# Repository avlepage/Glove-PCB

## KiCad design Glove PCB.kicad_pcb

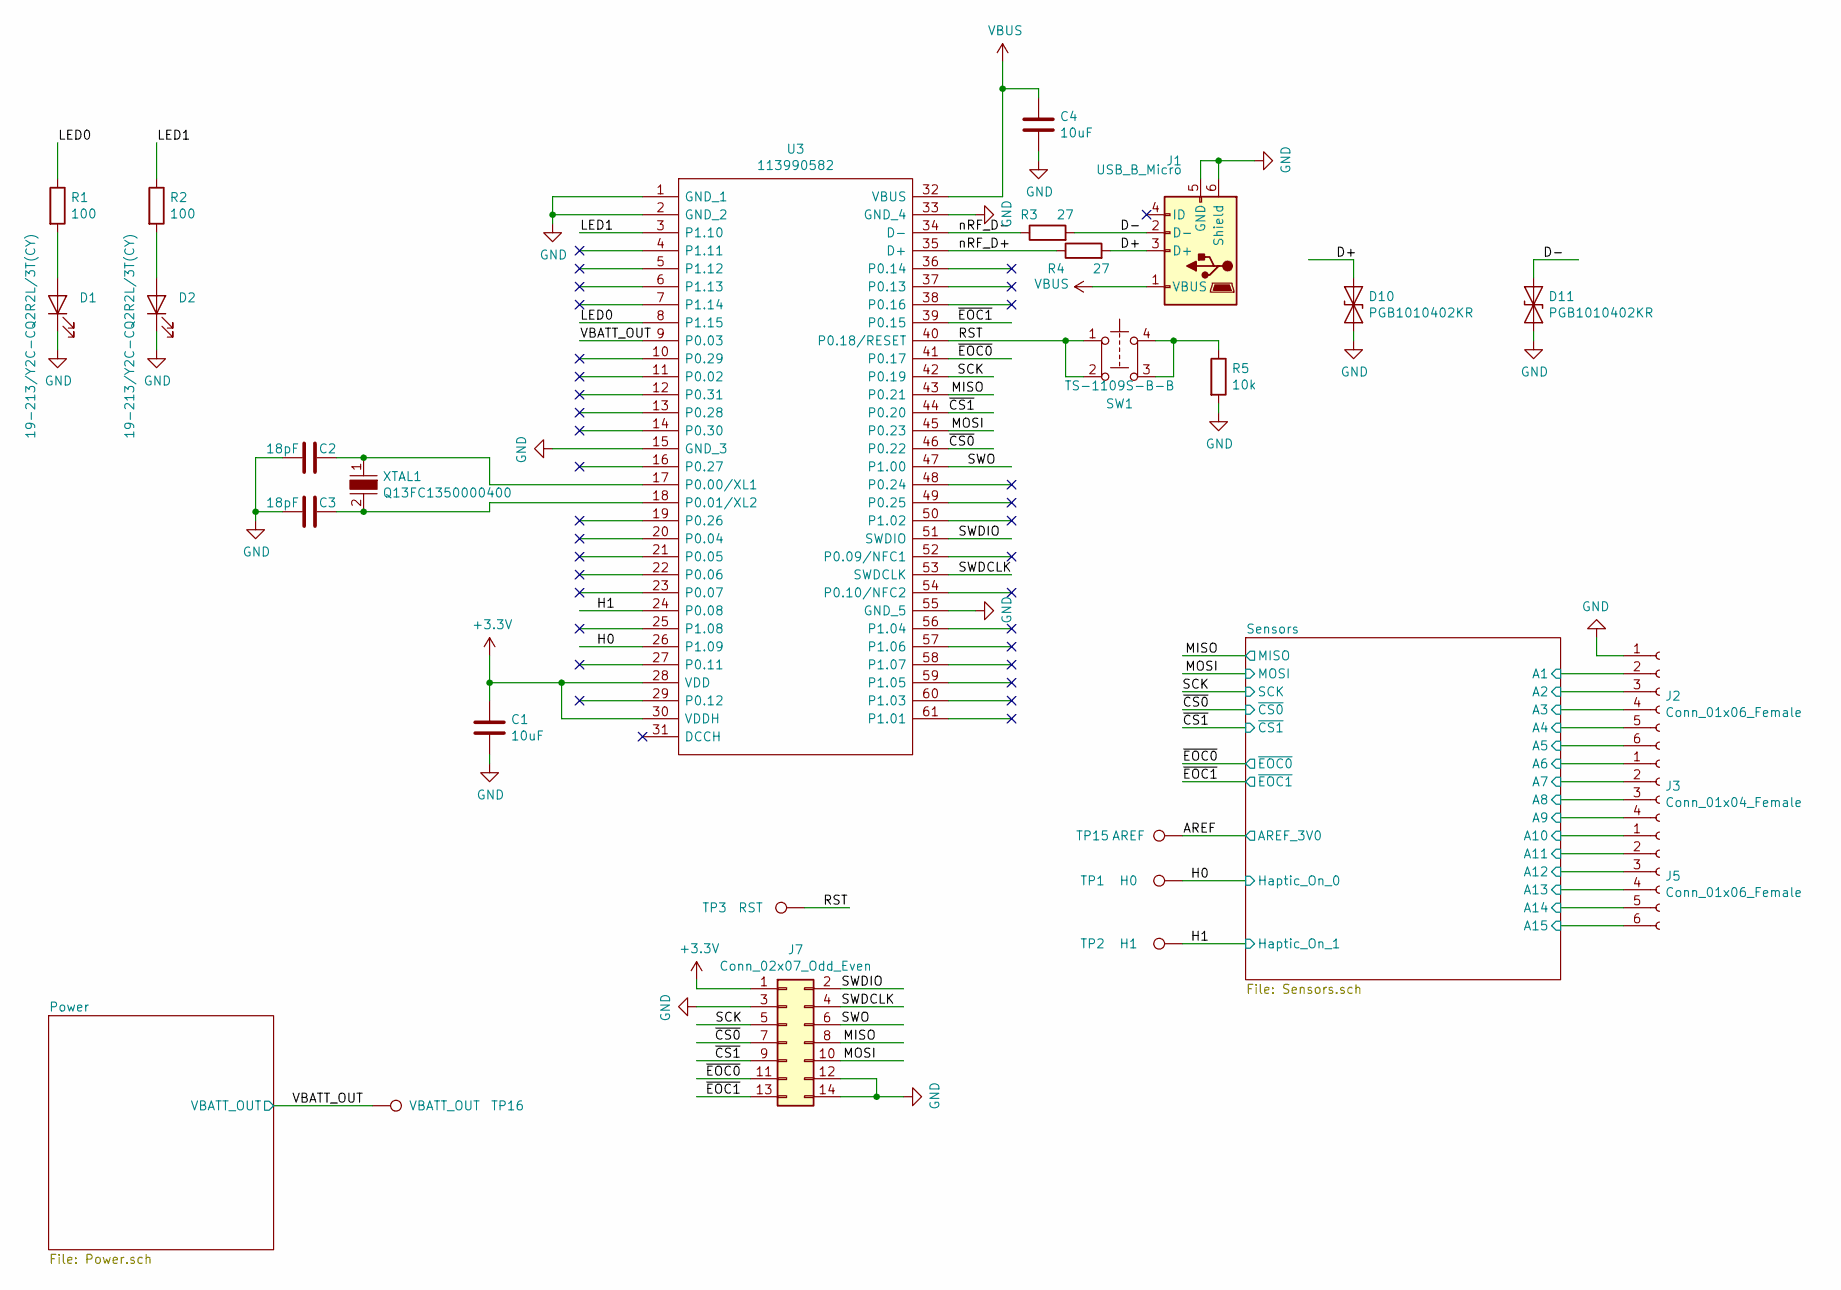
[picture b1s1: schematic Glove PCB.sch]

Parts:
C1, C4: 10uF; C_0603_HandSoldering; MPN CL10A106KP8NNNC; LCSC C19702
C2, C3: 18pF; C_0402; MPN 0402CG180J500NT; LCSC C1549
D1, D2: 19-213/Y2C-CQ2R2L/3T(CY); LED_0603_HandSoldering; MPN 19-213/Y2C-CQ2R2L/3T(CY); LCSC C72038
D10, D11: PGB1010402KR; D_0402_1005Metric; MPN PGB1010402KR; LCSC C10676
J1: USB_B_Micro; USB_Micro-B_10118194-0001LF
J2, J5: Conn_01x06_Female; 22-05-7065
J3: Conn_01x04_Female; 22-05-7045
J7: Conn_02x07_Odd_Even; PinHeader_2x07_P2.54mm_Vertical
R1, R2: 100; R_0603_HandSoldering; MPN 0603WAF1000T5E; LCSC C22775
R3, R4: 27; R_0603_1608Metric_Pad0.84x1.00mm_HandSolder; MPN 0603WAF270JT5E; LCSC C25190
R5: 10k; R_0402_1005Metric; MPN 0402WGF1002TCE; LCSC C25744
SW1: TS-1109S-B-B; Button; MPN TS-1109S-B-B; LCSC C480315
TP1: H0; TestPoint_Pad_D1.5mm
TP2: H1; TestPoint_Pad_D1.5mm
TP3: RST; TestPoint_Pad_D1.5mm
TP15: AREF; TestPoint_Pad_D1.5mm
TP16: VBATT_OUT; TestPoint_Pad_D1.5mm
U3: 113990582; Mouser Part Number 713-113990582
XTAL1: Q13FC1350000400; Crystal_SMD_G8-2pin_3.2x1.5mm; MPN Q13FC1350000400; Digi-Key_PN XC1617CT-ND

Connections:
+3V3: C1.1, J7.1, U3.28 (VDD), U3.30 (VDDH); also elsewhere on the board
/AREF: TP15.1; also elsewhere on the board
/D+: D10.1 (A1), J1.3 (D+), R4.2
/D-: D11.1 (A1), J1.2 (D-), R3.2
/H0: TP1.1, U3.26 (P1.09); also elsewhere on the board
/H1: TP2.1, U3.24 (P0.08); also elsewhere on the board
/LED0: R1.1, U3.8 (P1.15)
/LED1: R2.1, U3.3 (P1.10)
/MISO: J7.8, U3.43 (P0.21); also elsewhere on the board
/MOSI: J7.10, U3.45 (P0.23); also elsewhere on the board
/RST: SW1.1, SW1.2, TP3.1, U3.40 (P0.18/RESET); also elsewhere on the board
/SCK: J7.5, U3.42 (P0.19); also elsewhere on the board
/SWDCLK: J7.4, U3.53 (SWDCLK)
/SWDIO: J7.2, U3.51 (SWDIO)
/SWO: J7.6, U3.47 (P1.00)
/Sensors/A1: J2.2; also elsewhere on the board
/Sensors/A2: J2.3; also elsewhere on the board
/Sensors/A3: J2.4; also elsewhere on the board
/Sensors/A4: J2.5; also elsewhere on the board
/Sensors/A5: J2.6; also elsewhere on the board
/Sensors/A6: J3.1; also elsewhere on the board
/Sensors/A7: J3.2; also elsewhere on the board
/Sensors/A8: J3.3; also elsewhere on the board
/Sensors/A9: J3.4; also elsewhere on the board
/Sensors/A10: J5.1; also elsewhere on the board
/Sensors/A11: J5.2; also elsewhere on the board
/Sensors/A12: J5.3; also elsewhere on the board
/Sensors/A13: J5.4; also elsewhere on the board
/Sensors/A14: J5.5; also elsewhere on the board
/Sensors/A15: J5.6; also elsewhere on the board
/VBATT_OUT: TP16.1, U3.9 (P0.03); also elsewhere on the board
/nRF_D+: R4.1, U3.35 (D+)
/nRF_D-: R3.1, U3.34 (D-)
/~CS0: J7.7, U3.46 (P0.22); also elsewhere on the board
/~CS1: J7.9, U3.44 (P0.20); also elsewhere on the board
/~EOC0: J7.11, U3.41 (P0.17); also elsewhere on the board
/~EOC1: J7.13, U3.39 (P0.15); also elsewhere on the board
GND: C1.2, C2.2, C3.2, C4.2, D1.1 (K), D2.1 (K), D10.2 (A2), D11.2 (A2), J1.5 (GND), J1.6 (Shield), J2.1, J7.3, J7.12, J7.14, R5.2, U3.1 (GND_1), U3.2 (GND_2), U3.15 (GND_3), U3.33 (GND_4), U3.55 (GND_5); also elsewhere on the board
unnamed: C2.1, U3.17 (P0.00/XL1), XTAL1.1
unnamed: C3.1, U3.18 (P0.01/XL2), XTAL1.2
unnamed: D1.2 (A), R1.2
unnamed: D2.2 (A), R2.2
unnamed: R5.1, SW1.3, SW1.4
VBUS: C4.1, J1.1 (VBUS), U3.32 (VBUS); also elsewhere on the board

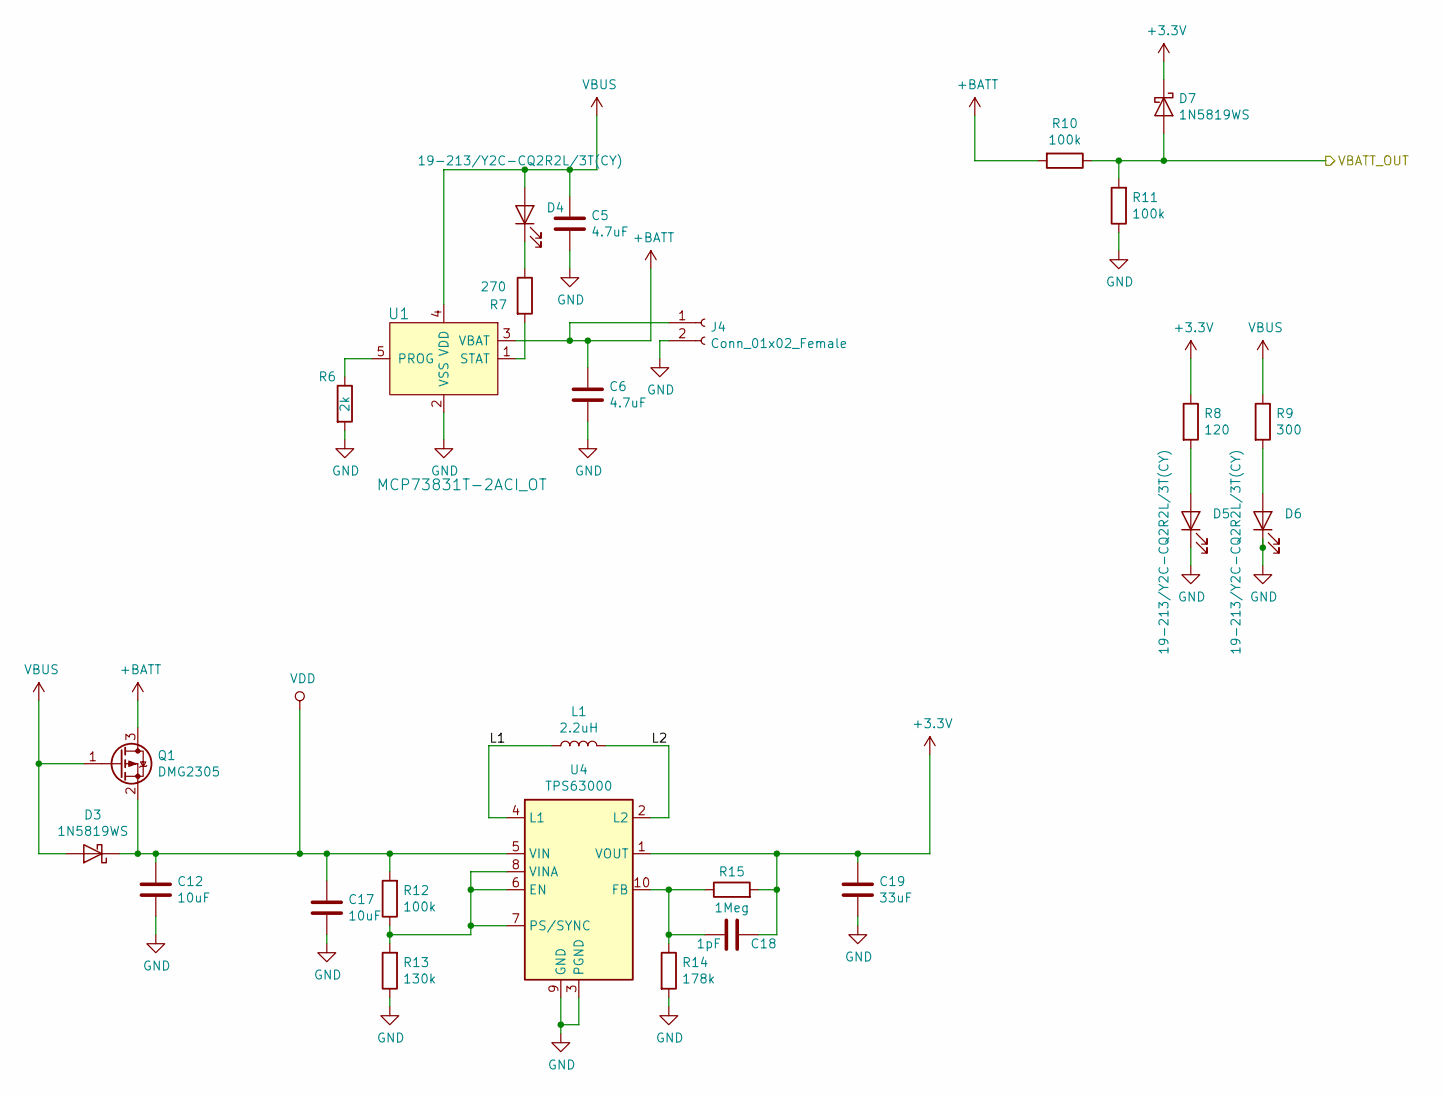
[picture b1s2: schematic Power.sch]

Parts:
C5, C6: 4.7uF; C_0603_HandSoldering; MPN CL10A475KO8NNNC; LCSC C19666
C12, C17: 10uF; C_0603_HandSoldering; MPN CL10A106KP8NNNC; LCSC C19702
C18: 1pF; C_0603_HandSoldering; MPN CL10C010CB8NNNC; LCSC C23969
C19: 33uF; C_0805_HandSoldering; MPN C2012X5R1A336MTJ00E; LCSC C342635
D3, D7: 1N5819WS; D_SOD-323; MPN 1N5819WS; LCSC C191023
D4, D5, D6: 19-213/Y2C-CQ2R2L/3T(CY); LED_0603_HandSoldering; MPN 19-213/Y2C-CQ2R2L/3T(CY); LCSC C72038
J4: Conn_01x02_Female; JST_PH_B2B-PH-SM4-TB_1x02_P2.00mm_Vertical
L1: 2.2uH; L_0805_HandSoldering; MPN MPH201210S2R2MT; LCSC C55755
Q1: DMG2305; SOT-23; MPN DMG2305UX-13; LCSC C144153
R6: 2k; R_0402_1005Metric; MPN 0402WGF2001TCE; LCSC C4109
R7: 270; R_0603_HandSoldering; MPN 0603WAF2700T5E; LCSC C22966
R8: 120; R_0603_HandSoldering; MPN 0603WAF1200T5E; LCSC C22787
R9: 300; R_0603_HandSoldering; MPN 0603WAF3000T5E; LCSC C23025
R10, R11, R12: 100k; R_0603_HandSoldering; MPN 0603WAF1003T5E; LCSC C25803
R13: 130k; R_0603_HandSoldering; MPN 0603WAF1303T5E; LCSC C22795
R14: 178k; R_0603_HandSoldering; MPN 0603WAF1783T5E; LCSC C22823
R15: 1Meg; R_0603_HandSoldering; MPN 0603WAF1004T5E; LCSC C22935
U1: MCP73831T-2ACI_OT; SOT-753; MPN MCP73831T-2ACI/OT; Digi-Key_PN MCP73831T-2ACI/OTCT-ND
U4: TPS63000; VSON-10-1EP_3x3mm_P0.5mm_EP1.65x2.4mm_ThermalVias; MPN TPS63000DRCR; LCSC C24966

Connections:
+3V3: C18.1, C19.1, D7.1 (K), R8.1, R15.2, U4.1 (VOUT); also elsewhere on the board
+BATT: C6.1, J4.1, Q1.3 (D), R10.2, U1.3 (VBAT)
/Power/L1: L1.1, U4.4 (L1)
/Power/L2: L1.2, U4.2 (L2)
/VBATT_OUT: D7.2 (A), R10.1, R11.2; also elsewhere on the board
GND: C5.2, C6.2, C12.2, C17.2, C19.2, D5.1 (K), D6.1 (K), J4.2, R6.2, R11.1, R13.1, R14.2, U1.2 (VSS), U4.3 (PGND), U4.9 (GND), U4.11 (PGND); also elsewhere on the board
unnamed: C18.2, R14.1, R15.1, U4.10 (FB)
unnamed: D4.1 (K), R7.1
unnamed: D5.2 (A), R8.2
unnamed: D6.2 (A), R9.2
unnamed: R6.1, U1.5 (PROG)
unnamed: R7.2, U1.1 (STAT)
unnamed: R12.1, R13.2, U4.6 (EN), U4.7 (PS/SYNC), U4.8 (VINA)
VBUS: C5.1, D3.2 (A), D4.2 (A), Q1.1 (G), R9.1, U1.4 (VDD); also elsewhere on the board
VDD: C12.1, C17.1, D3.1 (K), Q1.2 (S), R12.2, U4.5 (VIN); also elsewhere on the board

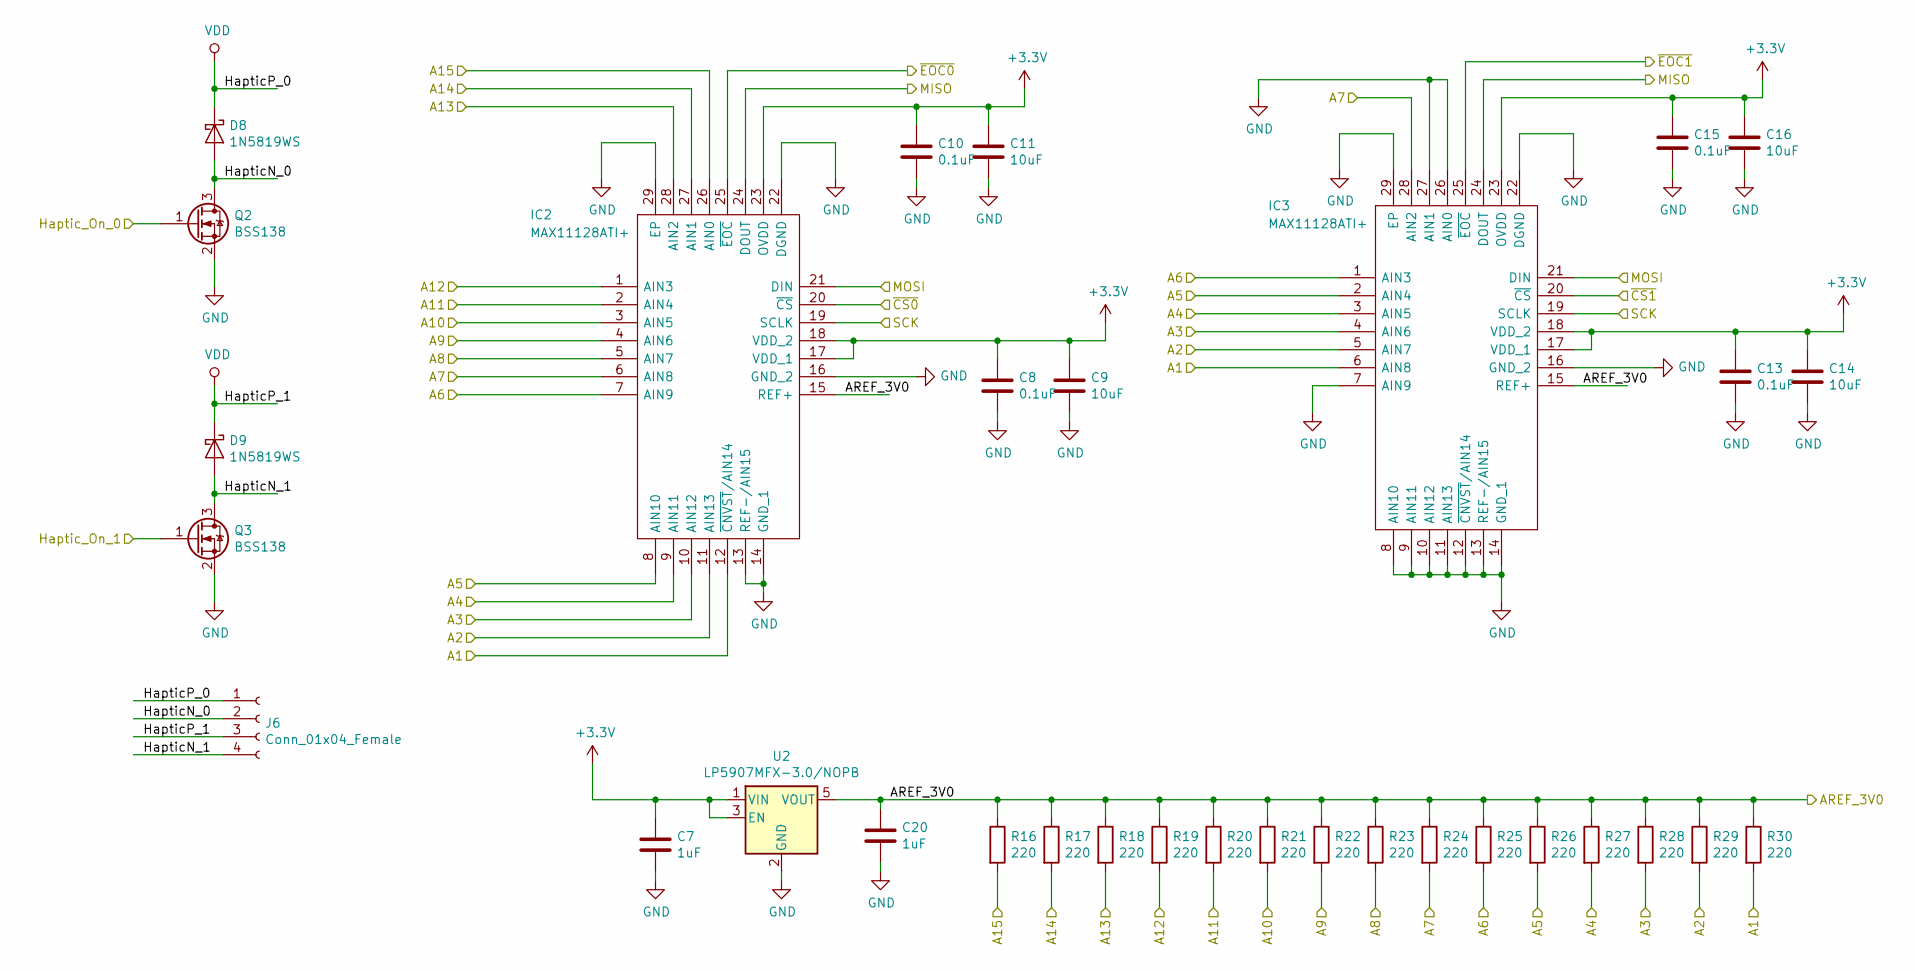
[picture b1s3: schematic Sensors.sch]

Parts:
C7, C20: 1uF; C_0603_HandSoldering; MPN CL10A105KB8NNNC; LCSC C15849
C8, C10, C13, C15: 0.1uF; C_0603_HandSoldering; MPN CC0603KRX7R9BB104; LCSC C14663
C9, C11, C14, C16: 10uF; C_0603_HandSoldering; MPN CL10A106KP8NNNC; LCSC C19702
D8, D9: 1N5819WS; D_SOD-323; MPN 1N5819WS; LCSC C191023
IC2, IC3: MAX11128ATI+; QFN50P500X500X80-29N; Mouser Part Number 700-MAX11128ATI+
J6: Conn_01x04_Female; 22-05-7045
Q2, Q3: BSS138; SOT-23; MPN BSS138; LCSC C52895
R16, R17, R18, R19, R20, R21, R22, R23, R24, R25, R26, R27, R28, R29, R30: 220; R_0603_HandSoldering; MPN 0603WAF2200T5E; LCSC C22962
U2: LP5907MFX-3.0/NOPB; SOT-23-5; MPN LP5907MFX-3.0/NOPB; LCSC C475492

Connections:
+3V3: C7.1, C8.1, C9.1, C10.1, C11.1, C13.1, C14.1, C15.1, C16.1, IC2.17 (VDD_1), IC2.18 (VDD_2), IC2.23 (OVDD), IC3.17 (VDD_1), IC3.18 (VDD_2), IC3.23 (OVDD), U2.1 (VIN), U2.3 (EN); also elsewhere on the board
/AREF: C20.1, IC2.15 (REF+), IC3.15 (REF+), R16.1, R17.1, R18.1, R19.1, R20.1, R21.1, R22.1, R23.1, R24.1, R25.1, R26.1, R27.1, R28.1, R29.1, R30.1, U2.5 (VOUT); also elsewhere on the board
/H0: Q2.1 (G); also elsewhere on the board
/H1: Q3.1 (G); also elsewhere on the board
/MISO: IC2.24 (DOUT), IC3.24 (DOUT); also elsewhere on the board
/MOSI: IC2.21 (DIN), IC3.21 (DIN); also elsewhere on the board
/SCK: IC2.19 (SCLK), IC3.19 (SCLK); also elsewhere on the board
/Sensors/A1: IC2.12 (~CNVST~/AIN14), IC3.6 (AIN8), R30.2; also elsewhere on the board
/Sensors/A2: IC2.11 (AIN13), IC3.5 (AIN7), R29.2; also elsewhere on the board
/Sensors/A3: IC2.10 (AIN12), IC3.4 (AIN6), R28.2; also elsewhere on the board
/Sensors/A4: IC2.9 (AIN11), IC3.3 (AIN5), R27.2; also elsewhere on the board
/Sensors/A5: IC2.8 (AIN10), IC3.2 (AIN4), R26.2; also elsewhere on the board
/Sensors/A6: IC2.7 (AIN9), IC3.1 (AIN3), R25.2; also elsewhere on the board
/Sensors/A7: IC2.6 (AIN8), IC3.28 (AIN2), R24.2; also elsewhere on the board
/Sensors/A8: IC2.5 (AIN7), R23.2; also elsewhere on the board
/Sensors/A9: IC2.4 (AIN6), R22.2; also elsewhere on the board
/Sensors/A10: IC2.3 (AIN5), R21.2; also elsewhere on the board
/Sensors/A11: IC2.2 (AIN4), R20.2; also elsewhere on the board
/Sensors/A12: IC2.1 (AIN3), R19.2; also elsewhere on the board
/Sensors/A13: IC2.28 (AIN2), R18.2; also elsewhere on the board
/Sensors/A14: IC2.27 (AIN1), R17.2; also elsewhere on the board
/Sensors/A15: IC2.26 (AIN0), R16.2; also elsewhere on the board
/Sensors/HapticN_0: D8.2 (A), J6.2, Q2.3 (D); also elsewhere on the board
/Sensors/HapticN_1: D9.2 (A), J6.4, Q3.3 (D); also elsewhere on the board
/~CS0: IC2.20 (~CS); also elsewhere on the board
/~CS1: IC3.20 (~CS); also elsewhere on the board
/~EOC0: IC2.25 (~EOC); also elsewhere on the board
/~EOC1: IC3.25 (~EOC); also elsewhere on the board
GND: C7.2, C8.2, C9.2, C10.2, C11.2, C13.2, C14.2, C15.2, C16.2, C20.2, IC2.13 (REF-/AIN15), IC2.14 (GND_1), IC2.16 (GND_2), IC2.22 (DGND), IC2.29 (EP), IC3.7 (AIN9), IC3.8 (AIN10), IC3.9 (AIN11), IC3.10 (AIN12), IC3.11 (AIN13), IC3.12 (~CNVST~/AIN14), IC3.13 (REF-/AIN15), IC3.14 (GND_1), IC3.16 (GND_2), IC3.22 (DGND), IC3.26 (AIN0), IC3.27 (AIN1), IC3.29 (EP), Q2.2 (S), Q3.2 (S), U2.2 (GND); also elsewhere on the board
VDD: D8.1 (K), D9.1 (K), J6.1, J6.3; also elsewhere on the board

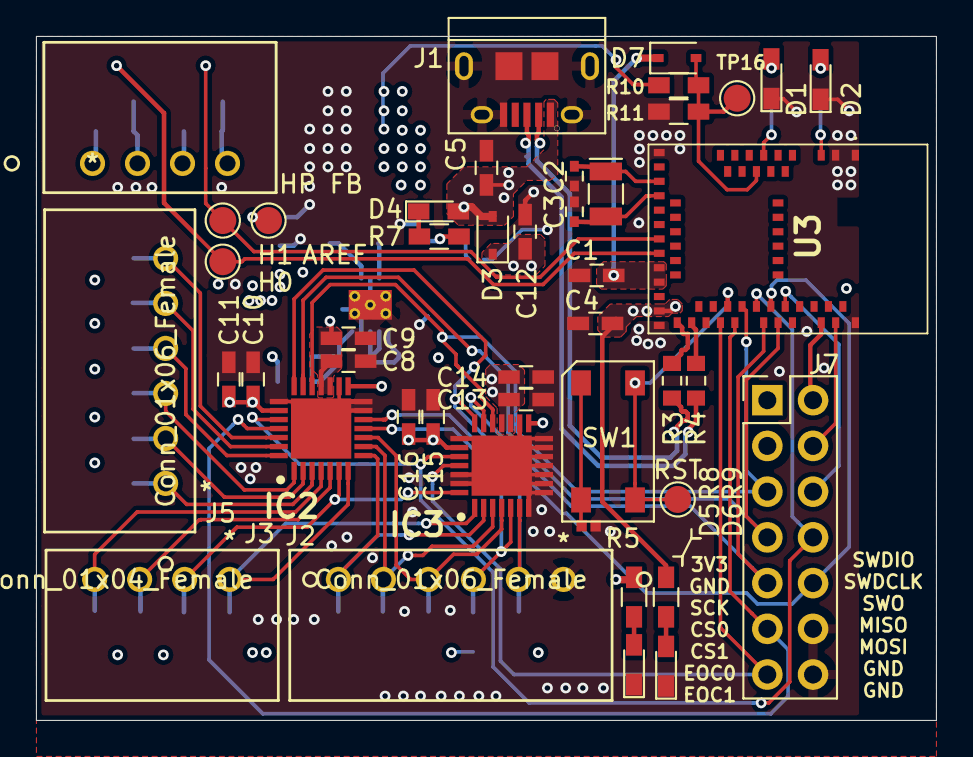
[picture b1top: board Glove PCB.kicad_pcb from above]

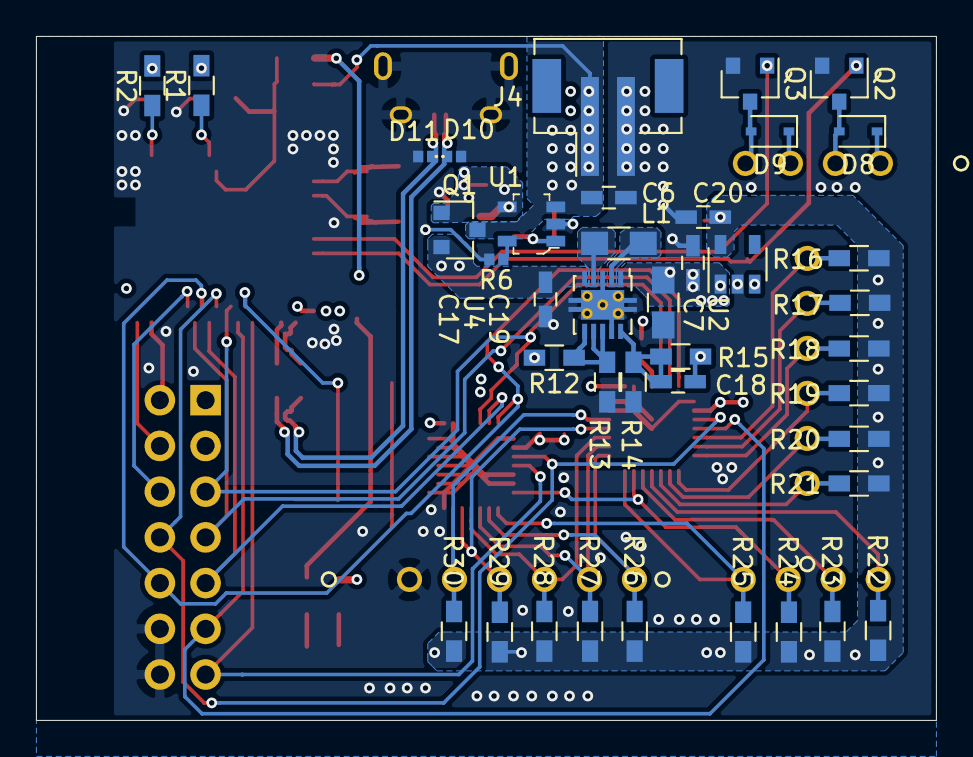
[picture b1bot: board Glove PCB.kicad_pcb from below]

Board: 4 copper layers, 50.0 x 38.0 mm, 85 parts (40 on the bottom side), 57 nets.

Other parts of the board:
HP FB: Conn_01x04_Female; 22-05-7045
RST: RST; TestPoint_Pad_D1.5mm

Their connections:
/RST: RST.1; also elsewhere on the board
/Sensors/HapticN_0: HP FB.2; also elsewhere on the board
/Sensors/HapticN_1: HP FB.4; also elsewhere on the board
VDD: HP FB.1, HP FB.3; also elsewhere on the board

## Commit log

2020-11-18 initial commit to Glove PCB. Schematic started, MCU main power sorted, still need to figure out sensors and actuators as well as the power.
2020-11-18 added LiPo charging circuit
2020-11-22 REAL COMMIT: Completed initial schematic. Added ADCs, Haptic FB circuits, test points, USB/Battery selection circuits.
2020-11-26 Added project and digikey footprints. Added mini-spox connectors.
2020-11-29 Placement done. Started layout.
2020-12-10 Changed to 4-layer board, added power shapes in layout.
2020-12-24 Added high side R for sensors and buck-boost. Replaced 3.0V VRef with LDO. BOM rev 1. Finished layout. TODO: Silkscreen.
2020-12-24 Filled copper zone priorities were frickle-frackled, they are fixed now. Still gotta do silk :(
2020-12-24 My nap was too long but finished silk.
2020-12-24 Add BOM Script and generated picknplace, BOM, & Gerbers. Sent to fabgit add -A!

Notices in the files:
parts and their libraries:
Copyright 2016 Accelerated Designs. All rights reserved.
